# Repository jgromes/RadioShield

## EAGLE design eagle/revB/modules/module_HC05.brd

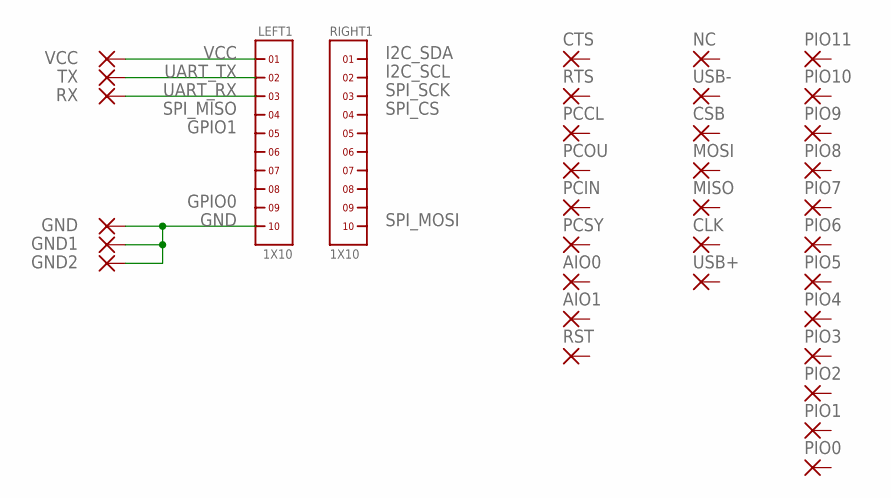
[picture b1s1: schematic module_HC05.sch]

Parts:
AIO0, AIO1: SMD1; SMD0,65-1,27
CLK: SMD1; SMD0,65-1,27
CSB: SMD1; SMD0,65-1,27
CTS: SMD1; SMD0,65-1,27
GND, GND1, GND2: SMD1; SMD0,65-1,27
LEFT1: 1X10
MISO: SMD1; SMD0,65-1,27
MOSI: SMD1; SMD0,65-1,27
NC: SMD1; SMD0,65-1,27
PCCL: SMD1; SMD0,65-1,27
PCIN: SMD1; SMD0,65-1,27
PCOU: SMD1; SMD0,65-1,27
PCSY: SMD1; SMD0,65-1,27
PIO0, PIO1, PIO2, PIO3, PIO4, PIO5, PIO6, PIO7, PIO8, PIO9, PIO10, PIO11: SMD1; SMD0,65-1,27
RIGHT1: 1X10
RST: SMD1; SMD0,65-1,27
RTS: SMD1; SMD0,65-1,27
RX: SMD1; SMD0,65-1,27
TX: SMD1; SMD0,65-1,27
USB+: SMD1; SMD0,65-1,27
USB-: SMD1; SMD0,65-1,27
VCC: SMD1; SMD0,65-1,27

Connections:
GND: GND.1, GND1.1, GND2.1, LEFT1.10
UART_RX: LEFT1.3, RX.1
UART_TX: LEFT1.2, TX.1
VCC: LEFT1.1, VCC.1

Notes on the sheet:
VCC
I2C_SDA
I2C_SCL
SPI_SCK
SPI_CS
SPI_MOSI
UART_TX
UART_RX
SPI_MISO
GPIO1
GPIO0
GND

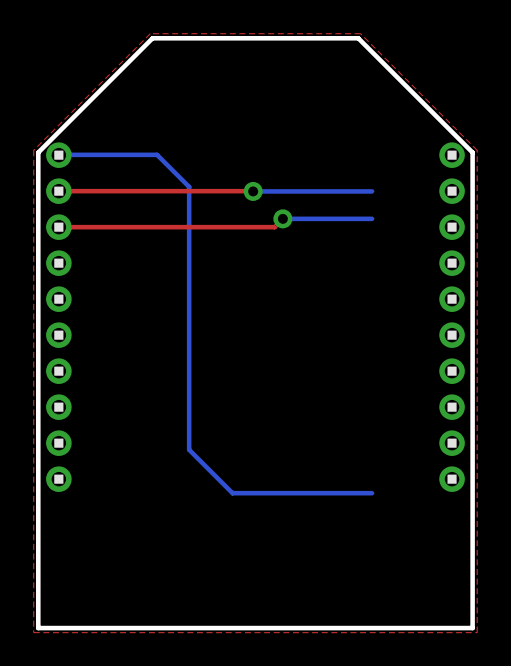
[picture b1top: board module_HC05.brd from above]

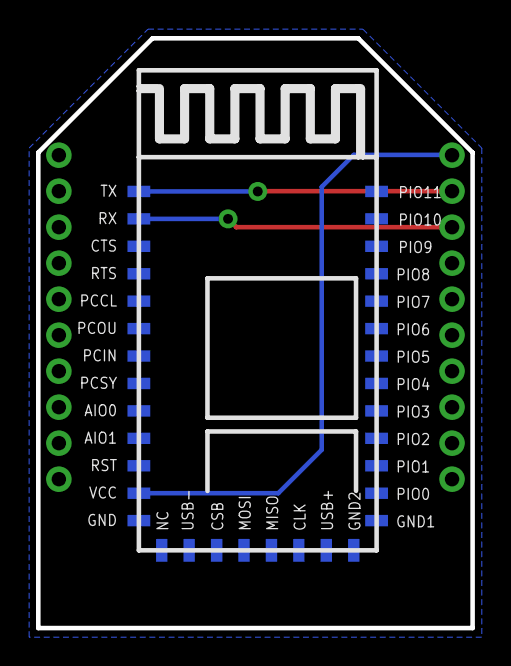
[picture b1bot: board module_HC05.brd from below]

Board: 2 copper layers, 24.1 x 32.8 mm, 36 parts (34 on the bottom side), 4 nets.

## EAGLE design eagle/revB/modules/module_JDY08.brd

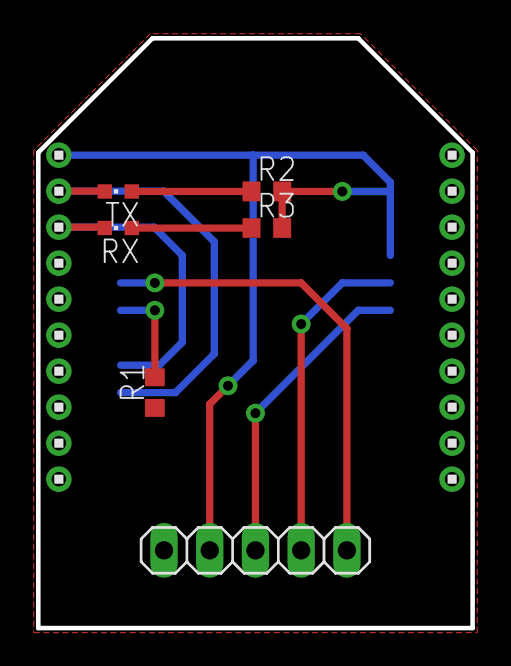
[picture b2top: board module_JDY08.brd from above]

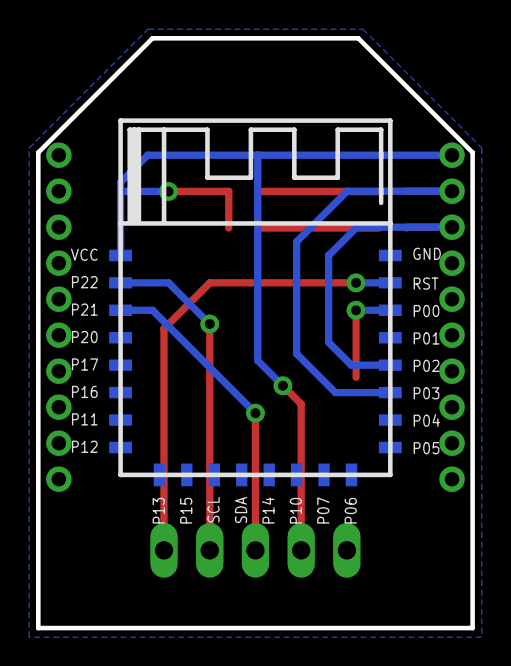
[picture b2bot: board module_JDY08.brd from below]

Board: 2 copper layers, 24.1 x 32.8 mm, 32 parts (24 on the bottom side), 10 nets.

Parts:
GND: SMD0,65-1,27
JP1: 1X05
LEFT1: 1X10
P00, P01, P02, P03, P04, P05, P06, P07, P10, P11, P12, P13, P14, P15, P16, P17, P20, P21, P22: SMD0,65-1,27
R1, R2, R3: 1K; R0603
RIGHT1: 1X10
RST: SMD0,65-1,27
RX: CHIPLED_0603
SCL: SMD0,65-1,27
SDA: SMD0,65-1,27
TX: CHIPLED_0603
VCC: SMD0,65-1,27

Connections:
GND: GND.1, JP1.1, LEFT1.10, R1.1
unnamed: JP1.5, RST.1
unnamed: JP1.3, P21.1
unnamed: JP1.4, P22.1
unnamed: P00.1, R1.2
unnamed: LEFT1.3, P02.1, RX.C
unnamed: LEFT1.2, P03.1, TX.C
unnamed: R2.1, TX.A
unnamed: R3.1, RX.A
VCC: JP1.2, LEFT1.1, R2.2, R3.2, VCC.1

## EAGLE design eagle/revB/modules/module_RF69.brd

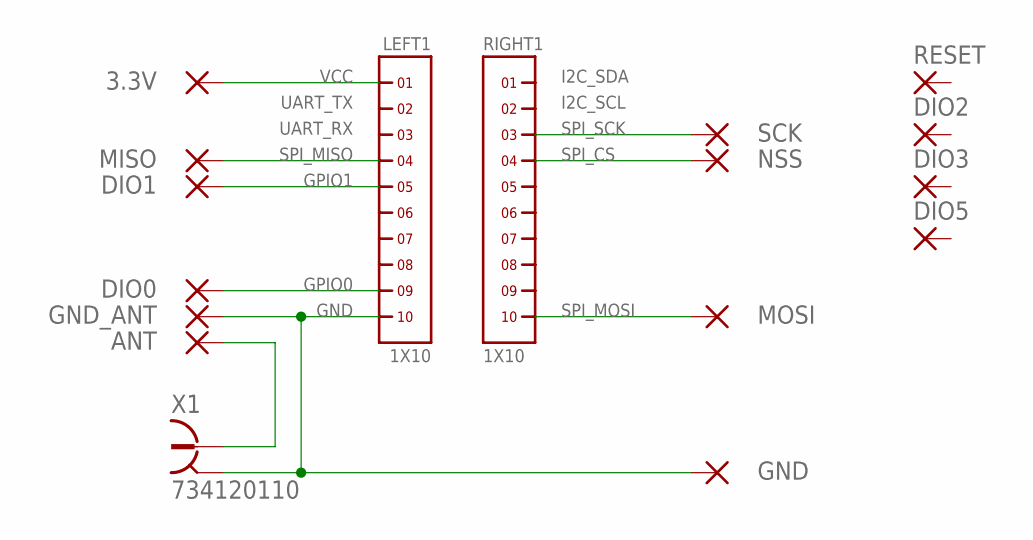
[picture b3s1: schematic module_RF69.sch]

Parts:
3.3V: SMD2; SMD1,27-2,54
ANT: SMD2; SMD1,27-2,54
DIO0, DIO1, DIO2, DIO3, DIO5: SMD2; SMD1,27-2,54
GND: SMD2; SMD1,27-2,54
GND_ANT: SMD2; SMD1,27-2,54
LEFT1: 1X10
MISO: SMD2; SMD1,27-2,54
MOSI: SMD2; SMD1,27-2,54
NSS: SMD2; SMD1,27-2,54
RESET: SMD2; SMD1,27-2,54
RIGHT1: 1X10
SCK: SMD2; SMD1,27-2,54
X1: 734120110

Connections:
ANT: ANT.1, X1.1
GND: GND.1, GND_ANT.1, LEFT1.10, X1.S@1 (2), X1.S@2 (2), X1.S@3 (2)
INT0: DIO0.1, LEFT1.9
INT1: DIO1.1, LEFT1.5
SPI_CS: NSS.1, RIGHT1.4
SPI_MISO: LEFT1.4, MISO.1
SPI_MOSI: MOSI.1, RIGHT1.10
SPI_SCK: RIGHT1.3, SCK.1
VCC: 3.3V.1, LEFT1.1

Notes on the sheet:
VCC
UART_TX
UART_RX
SPI_MISO
GPIO1
GND
GPIO0
SPI_MOSI
I2C_SDA
I2C_SCL
SPI_SCK
SPI_CS

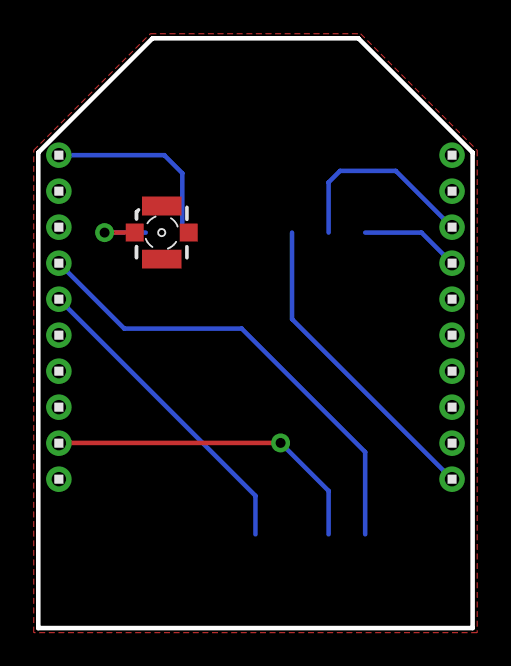
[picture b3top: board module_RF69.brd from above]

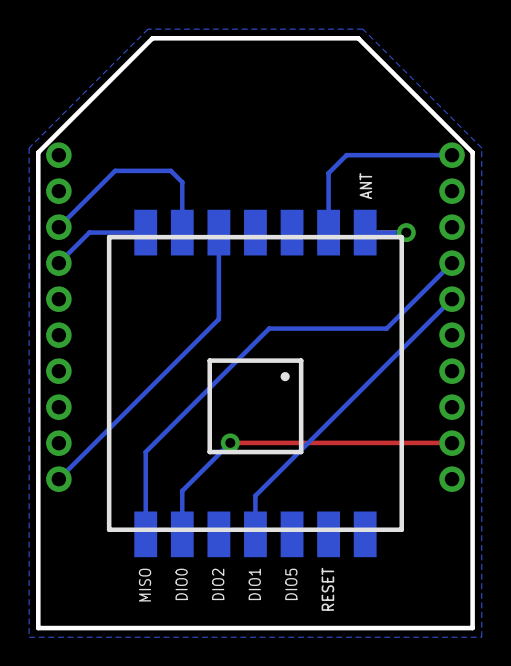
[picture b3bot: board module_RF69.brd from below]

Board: 2 copper layers, 24.1 x 32.8 mm, 17 parts (14 on the bottom side), 9 nets.

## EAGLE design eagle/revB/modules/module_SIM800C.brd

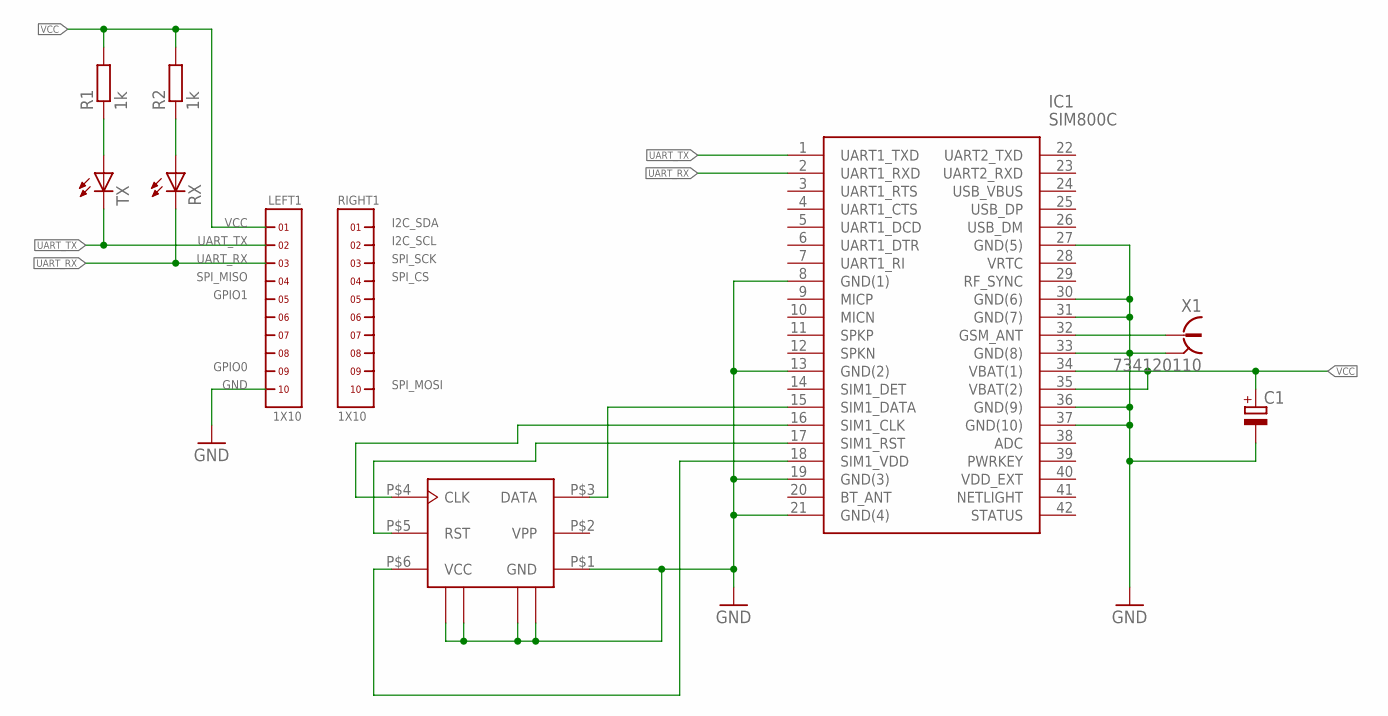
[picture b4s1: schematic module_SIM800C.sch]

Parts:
C1: CPOL-EUSMCD; SMC_D
IC1: SIM800C
LEFT1: 1X10
R1, R2: 1k; R0603
RIGHT1: 1X10
RX: LEDCHIPLED_0603; CHIPLED_0603
TX: LEDCHIPLED_0603; CHIPLED_0603
U$1: C707-10M006-136-2
X1: 734120110

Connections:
GND: C1.-, IC1.8 (GND(1)), IC1.13 (GND(2)), IC1.19 (GND(3)), IC1.21 (GND(4)), IC1.27 (GND(5)), IC1.30 (GND(6)), IC1.31 (GND(7)), IC1.33 (GND(8)), IC1.36 (GND(9)), IC1.37 (GND(10)), LEFT1.10, U$1.P$1 (GND), U$1.P$7 (GND1), U$1.P$8 (GND2), U$1.P$9 (GND3), U$1.P$10 (GND4), X1.S@1 (2), X1.S@2 (2), X1.S@3 (2)
unnamed: IC1.32 (GSM_ANT), X1.1
unnamed: R1.1, TX.A
unnamed: R2.1, RX.A
unnamed: IC1.15 (SIM1_DATA), U$1.P$3 (DATA)
unnamed: IC1.16 (SIM1_CLK), U$1.P$4 (CLK)
unnamed: IC1.17 (SIM1_RST), U$1.P$5 (RST)
unnamed: IC1.18 (SIM1_VDD), U$1.P$6 (VCC)
UART_RX: IC1.2 (UART1_RXD), LEFT1.3, RX.C
UART_TX: IC1.1 (UART1_TXD), LEFT1.2, TX.C
VCC: C1.+, IC1.34 (VBAT(1)), IC1.35 (VBAT(2)), LEFT1.1, R1.2, R2.2
VPP: U$1.P$2 (VPP)

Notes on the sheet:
VCC
UART_TX
UART_RX
SPI_MISO
GPIO1
GND
GPIO0
SPI_MOSI
I2C_SDA
I2C_SCL
SPI_SCK
SPI_CS

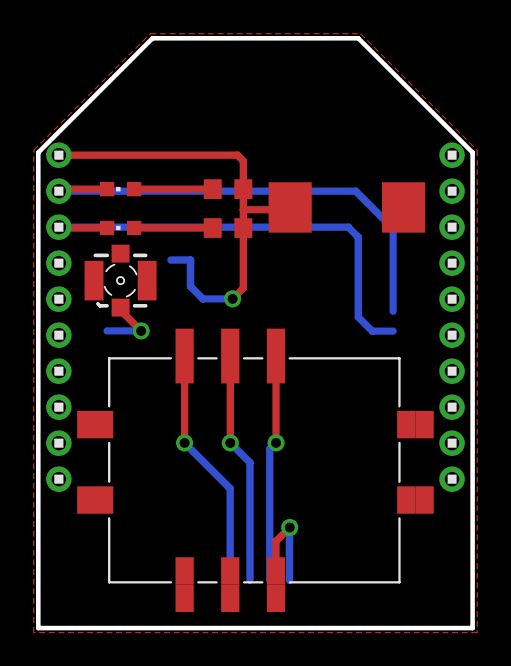
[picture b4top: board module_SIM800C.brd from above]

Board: 2 copper layers, 24.1 x 32.8 mm, 10 parts (1 on the bottom side), 11 nets.

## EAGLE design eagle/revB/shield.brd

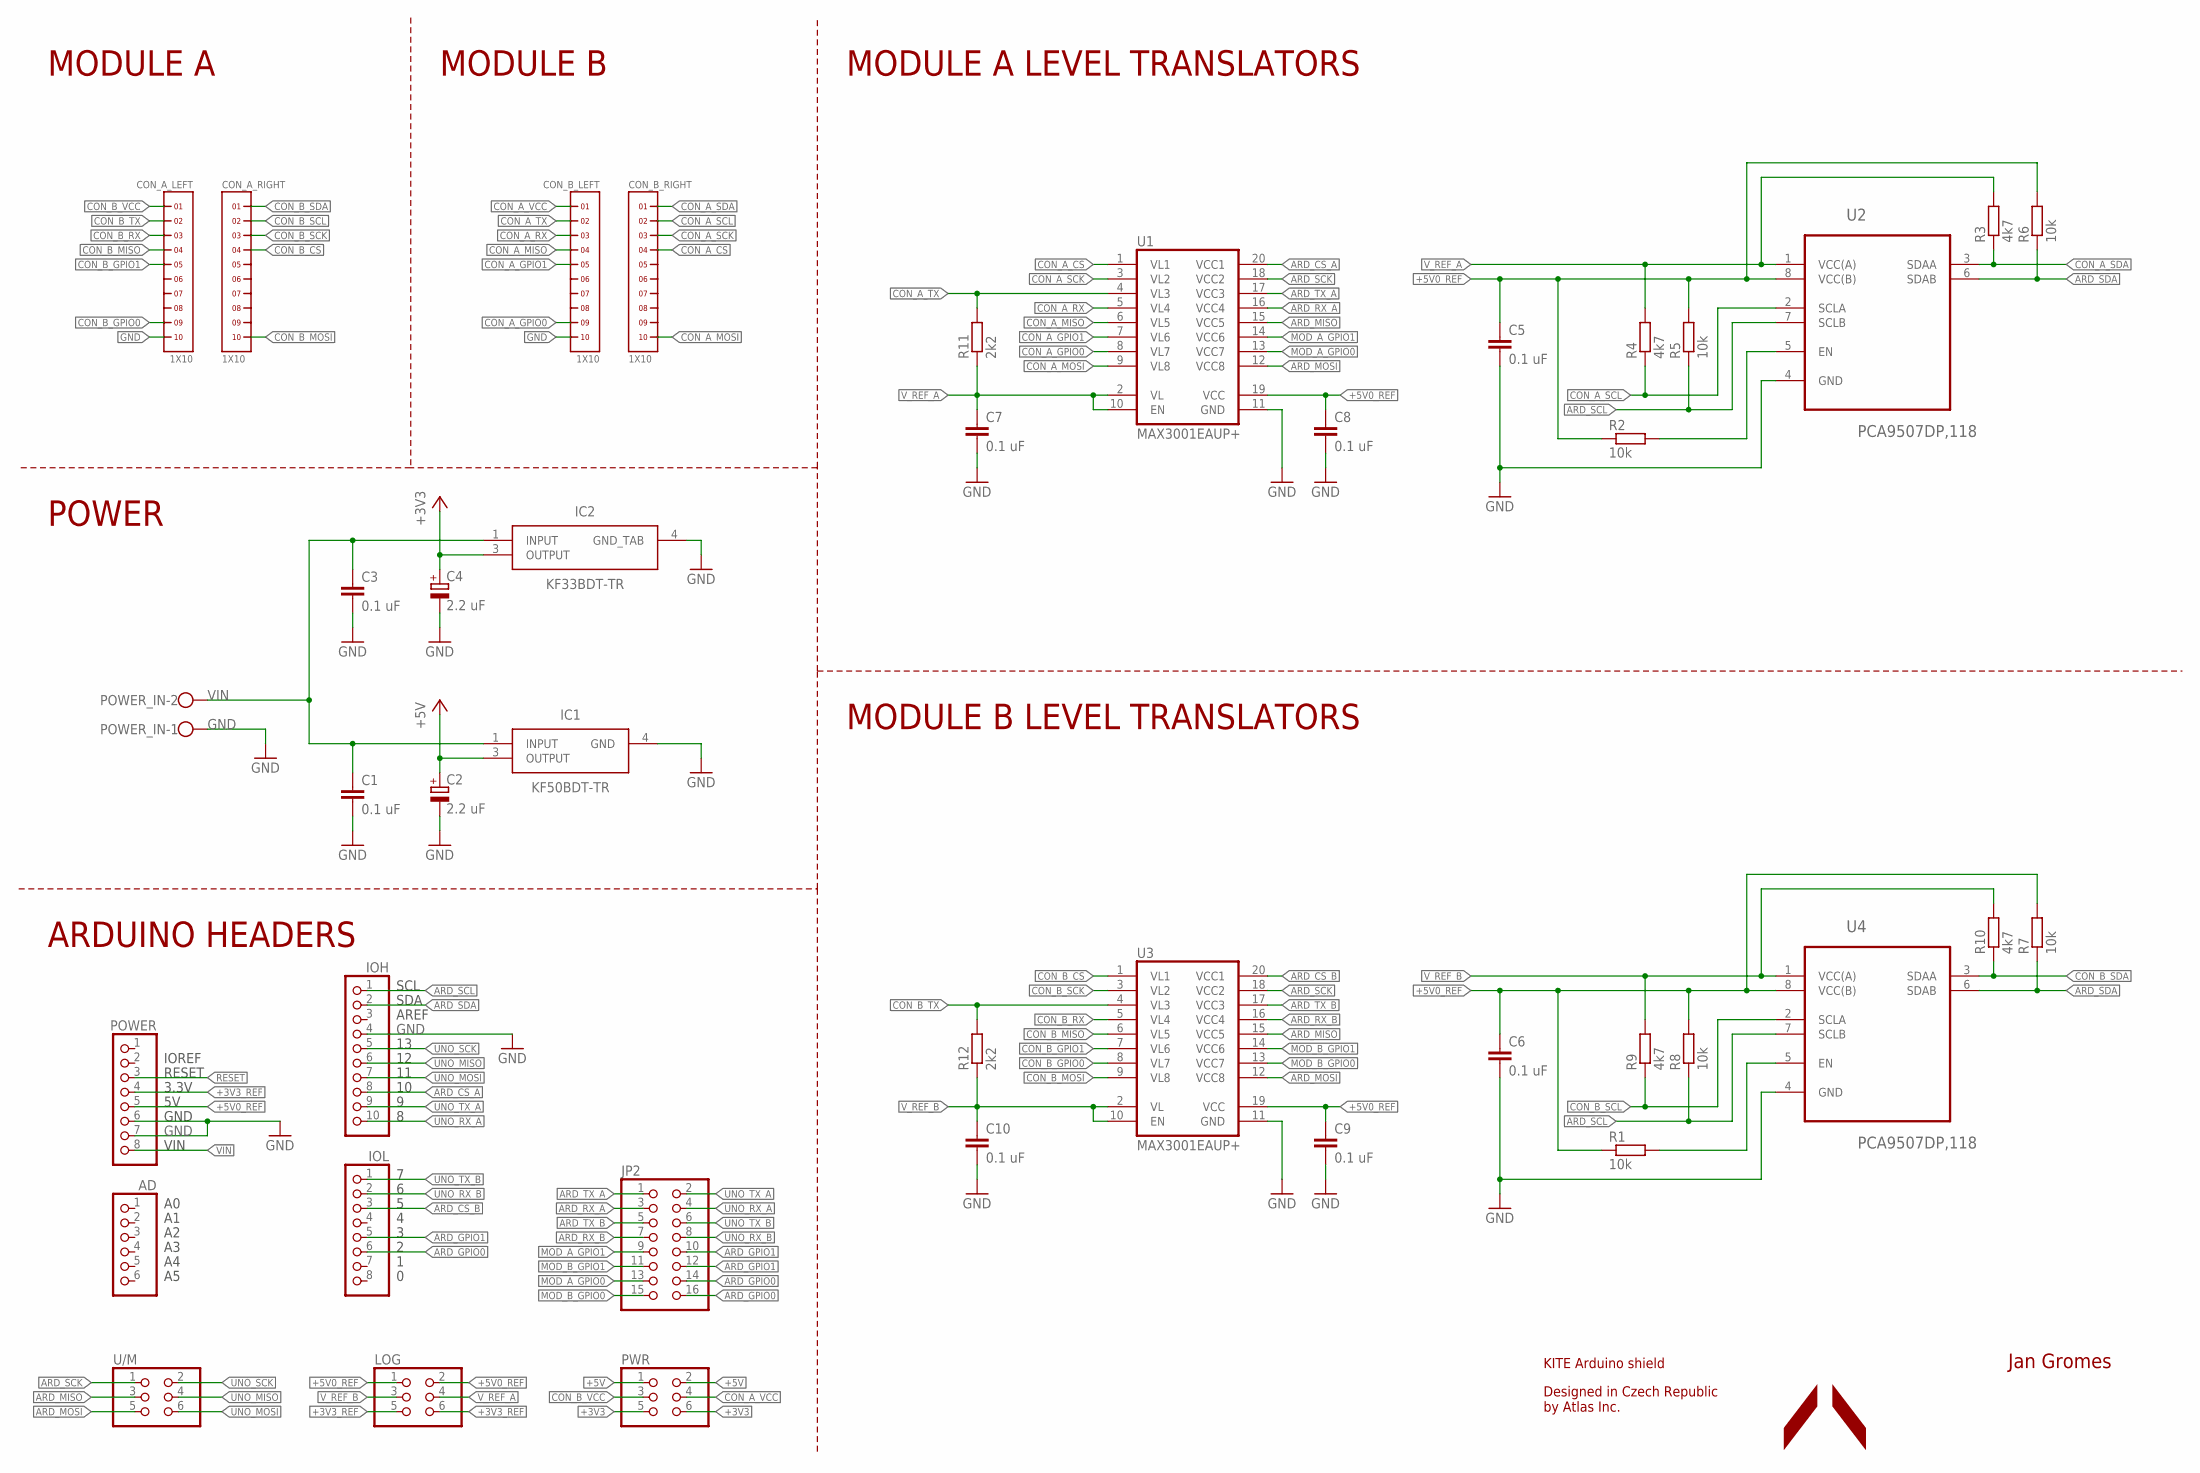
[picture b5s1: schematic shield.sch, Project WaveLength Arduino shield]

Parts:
AD: PINHD-1X6; 1X06
C1, C3, C5, C6, C7, C8, C9, C10: 0.1 uF; C0603
C2, C4: 2.2 uF; SMC_A
CON_A_LEFT: 1X10
CON_A_RIGHT: 1X10
CON_B_LEFT: 1X10
CON_B_RIGHT: 1X10
IC1: KF50BDT-TR; TO228P972X240-3N
IC2: KF33BDT-TR; TO228P972X240-3N
IOH: PINHD-1X10; 1X10
IOL: PINHD-1X8; 1X08
JP2: PINHD-2X8; 2X08
LOG: PINHD-2X3; 2X03
POWER: PINHD-1X8; 1X08
POWER_IN: W237-102
PWR: PINHD-2X3; 2X03
R1, R2, R5, R6, R7, R8: 10k; R0603
R3, R4, R9, R10: 4k7; R0603
R11, R12: 2k2; R0603
U1, U3: MAX3001EAUP+; TSSOP20
U2, U4: PCA9507DP,118; SOP65P490X110-8N
U/M: PINHD-2X3; 2X03

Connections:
+3V3: C4.+, IC2.3 (OUTPUT), PWR.5, PWR.6
+3V3_REF: LOG.5, LOG.6, POWER.4
+5V: C2.+, IC1.3 (OUTPUT), PWR.1, PWR.2
+5V0_REF: C5.1, C6.1, C8.1, C9.1, LOG.1, LOG.2, POWER.5, R1.1, R2.1, R5.2, R6.2, R7.2, R8.2, U1.19 (VCC), U2.8 (VCC(B)), U3.19 (VCC), U4.8 (VCC(B))
ARD_CS_A: IOH.8, U1.20 (VCC1)
ARD_CS_B: IOL.3, U3.20 (VCC1)
ARD_GPIO0: IOL.6, JP2.14, JP2.16
ARD_GPIO1: IOL.5, JP2.10, JP2.12
ARD_MISO: U1.15 (VCC5), U3.15 (VCC5), U/M.3
ARD_MOSI: U1.12 (VCC8), U3.12 (VCC8), U/M.5
ARD_RX_A: JP2.3, U1.16 (VCC4)
ARD_RX_B: JP2.7, U3.16 (VCC4)
ARD_SCK: U1.18 (VCC2), U3.18 (VCC2), U/M.1
ARD_SCL: IOH.1, R5.1, R8.1, U2.7 (SCLB), U4.7 (SCLB)
ARD_SDA: IOH.2, R6.1, R7.1, U2.6 (SDAB), U4.6 (SDAB)
ARD_TX_A: JP2.1, U1.17 (VCC3)
ARD_TX_B: JP2.5, U3.17 (VCC3)
CON_A_CS: CON_B_RIGHT.4, U1.1 (VL1)
CON_A_GPIO0: CON_B_LEFT.9, U1.8 (VL7)
CON_A_GPIO1: CON_B_LEFT.5, U1.7 (VL6)
CON_A_MISO: CON_B_LEFT.4, U1.6 (VL5)
CON_A_MOSI: CON_B_RIGHT.10, U1.9 (VL8)
CON_A_RX: CON_B_LEFT.3, U1.5 (VL4)
CON_A_SCK: CON_B_RIGHT.3, U1.3 (VL2)
CON_A_SCL: CON_B_RIGHT.2, R4.1, U2.2 (SCLA)
CON_A_SDA: CON_B_RIGHT.1, R3.1, U2.3 (SDAA)
CON_A_TX: CON_B_LEFT.2, R11.2, U1.4 (VL3)
CON_A_VCC: CON_B_LEFT.1, PWR.4
CON_B_CS: CON_A_RIGHT.4, U3.1 (VL1)
CON_B_GPIO0: CON_A_LEFT.9, U3.8 (VL7)
CON_B_GPIO1: CON_A_LEFT.5, U3.7 (VL6)
CON_B_MISO: CON_A_LEFT.4, U3.6 (VL5)
CON_B_MOSI: CON_A_RIGHT.10, U3.9 (VL8)
CON_B_RX: CON_A_LEFT.3, U3.5 (VL4)
CON_B_SCK: CON_A_RIGHT.3, U3.3 (VL2)
CON_B_SCL: CON_A_RIGHT.2, R9.1, U4.2 (SCLA)
CON_B_SDA: CON_A_RIGHT.1, R10.1, U4.3 (SDAA)
CON_B_TX: CON_A_LEFT.2, R12.2, U3.4 (VL3)
CON_B_VCC: CON_A_LEFT.1, PWR.3
GND: C1.2, C2.-, C3.2, C4.-, C5.2, C6.2, C7.2, C8.2, C9.2, C10.2, CON_A_LEFT.10, CON_B_LEFT.10, IC1.4 (GND), IC2.4 (GND_TAB), IOH.4, POWER.6, POWER.7, POWER_IN.1, U1.11 (GND), U2.4 (GND), U3.11 (GND), U4.4 (GND)
MOD_A_GPIO0: JP2.13, U1.13 (VCC7)
MOD_A_GPIO1: JP2.9, U1.14 (VCC6)
MOD_B_GPIO0: JP2.15, U3.13 (VCC7)
MOD_B_GPIO1: JP2.11, U3.14 (VCC6)
unnamed: R2.2, U2.5 (EN)
unnamed: R1.2, U4.5 (EN)
RESET: POWER.3
UNO_MISO: IOH.6, U/M.4
UNO_MOSI: IOH.7, U/M.6
UNO_RX_A: IOH.10, JP2.4
UNO_RX_B: IOL.2, JP2.8
UNO_SCK: IOH.5, U/M.2
UNO_TX_A: IOH.9, JP2.2
UNO_TX_B: IOL.1, JP2.6
VIN: C1.1, C3.1, IC1.1 (INPUT), IC2.1 (INPUT), POWER.8, POWER_IN.2
V_REF_A: C7.1, LOG.4, R3.2, R4.2, R11.1, U1.2 (VL), U1.10 (EN), U2.1 (VCC(A))
V_REF_B: C10.1, LOG.3, R9.2, R10.2, R12.1, U3.2 (VL), U3.10 (EN), U4.1 (VCC(A))

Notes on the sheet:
Jan Gromes
AREF
SDA
SCL
VIN
GND
3.3V
RESET
IOREF
MODULE B LEVEL TRANSLATORS
MODULE A LEVEL TRANSLATORS
MODULE A
MODULE B
POWER
ARDUINO HEADERS
KITE Arduino shield
Designed in Czech Republic by Atlas Inc.

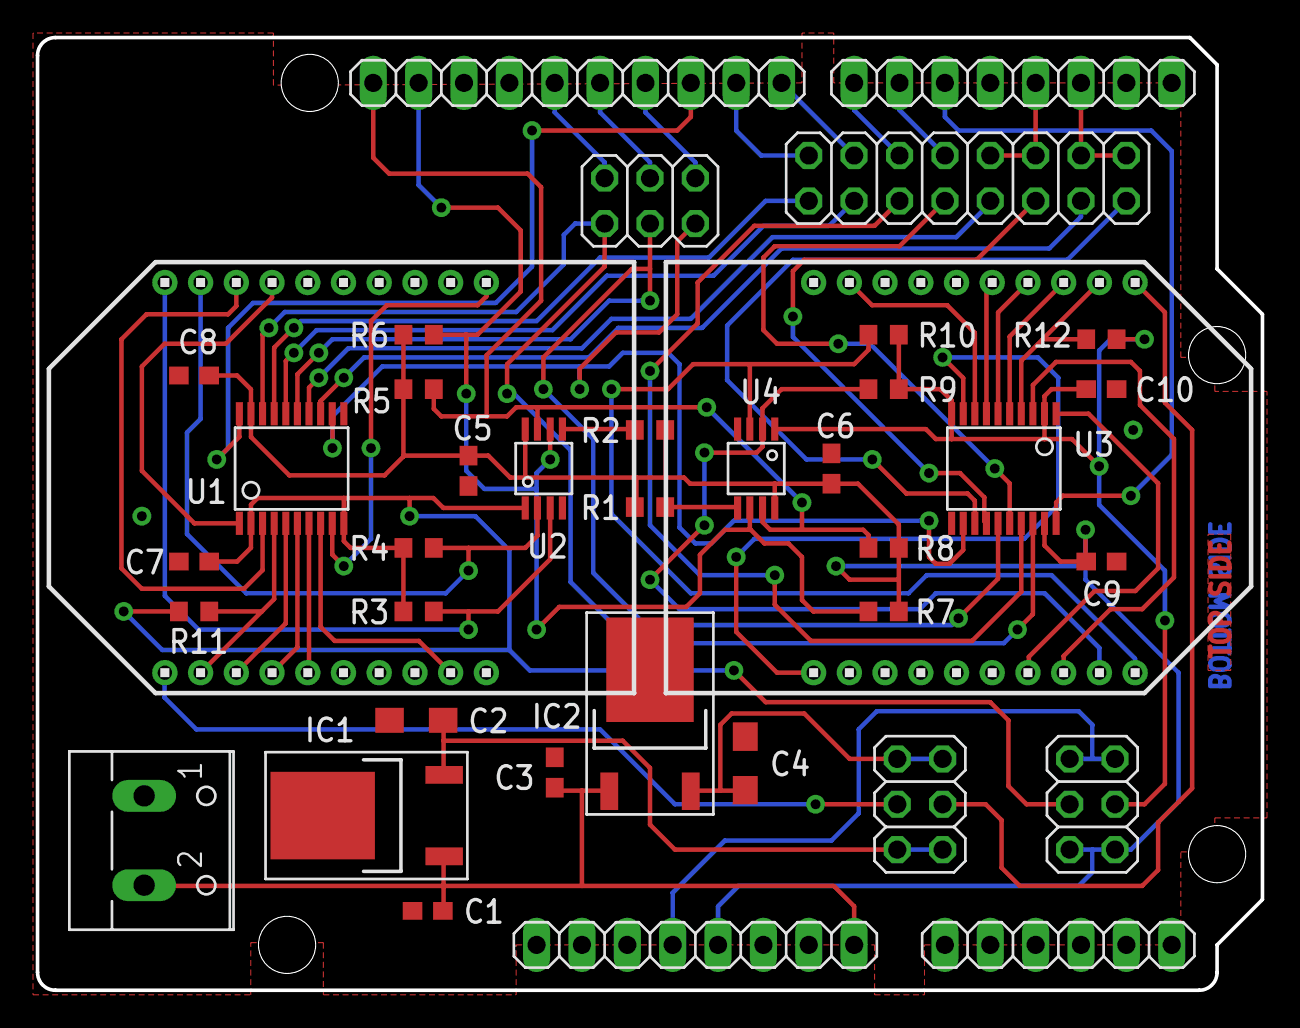
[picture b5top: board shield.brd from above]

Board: 2 copper layers, 68.6 x 53.3 mm, 41 parts (0 on the bottom side), 56 nets.
